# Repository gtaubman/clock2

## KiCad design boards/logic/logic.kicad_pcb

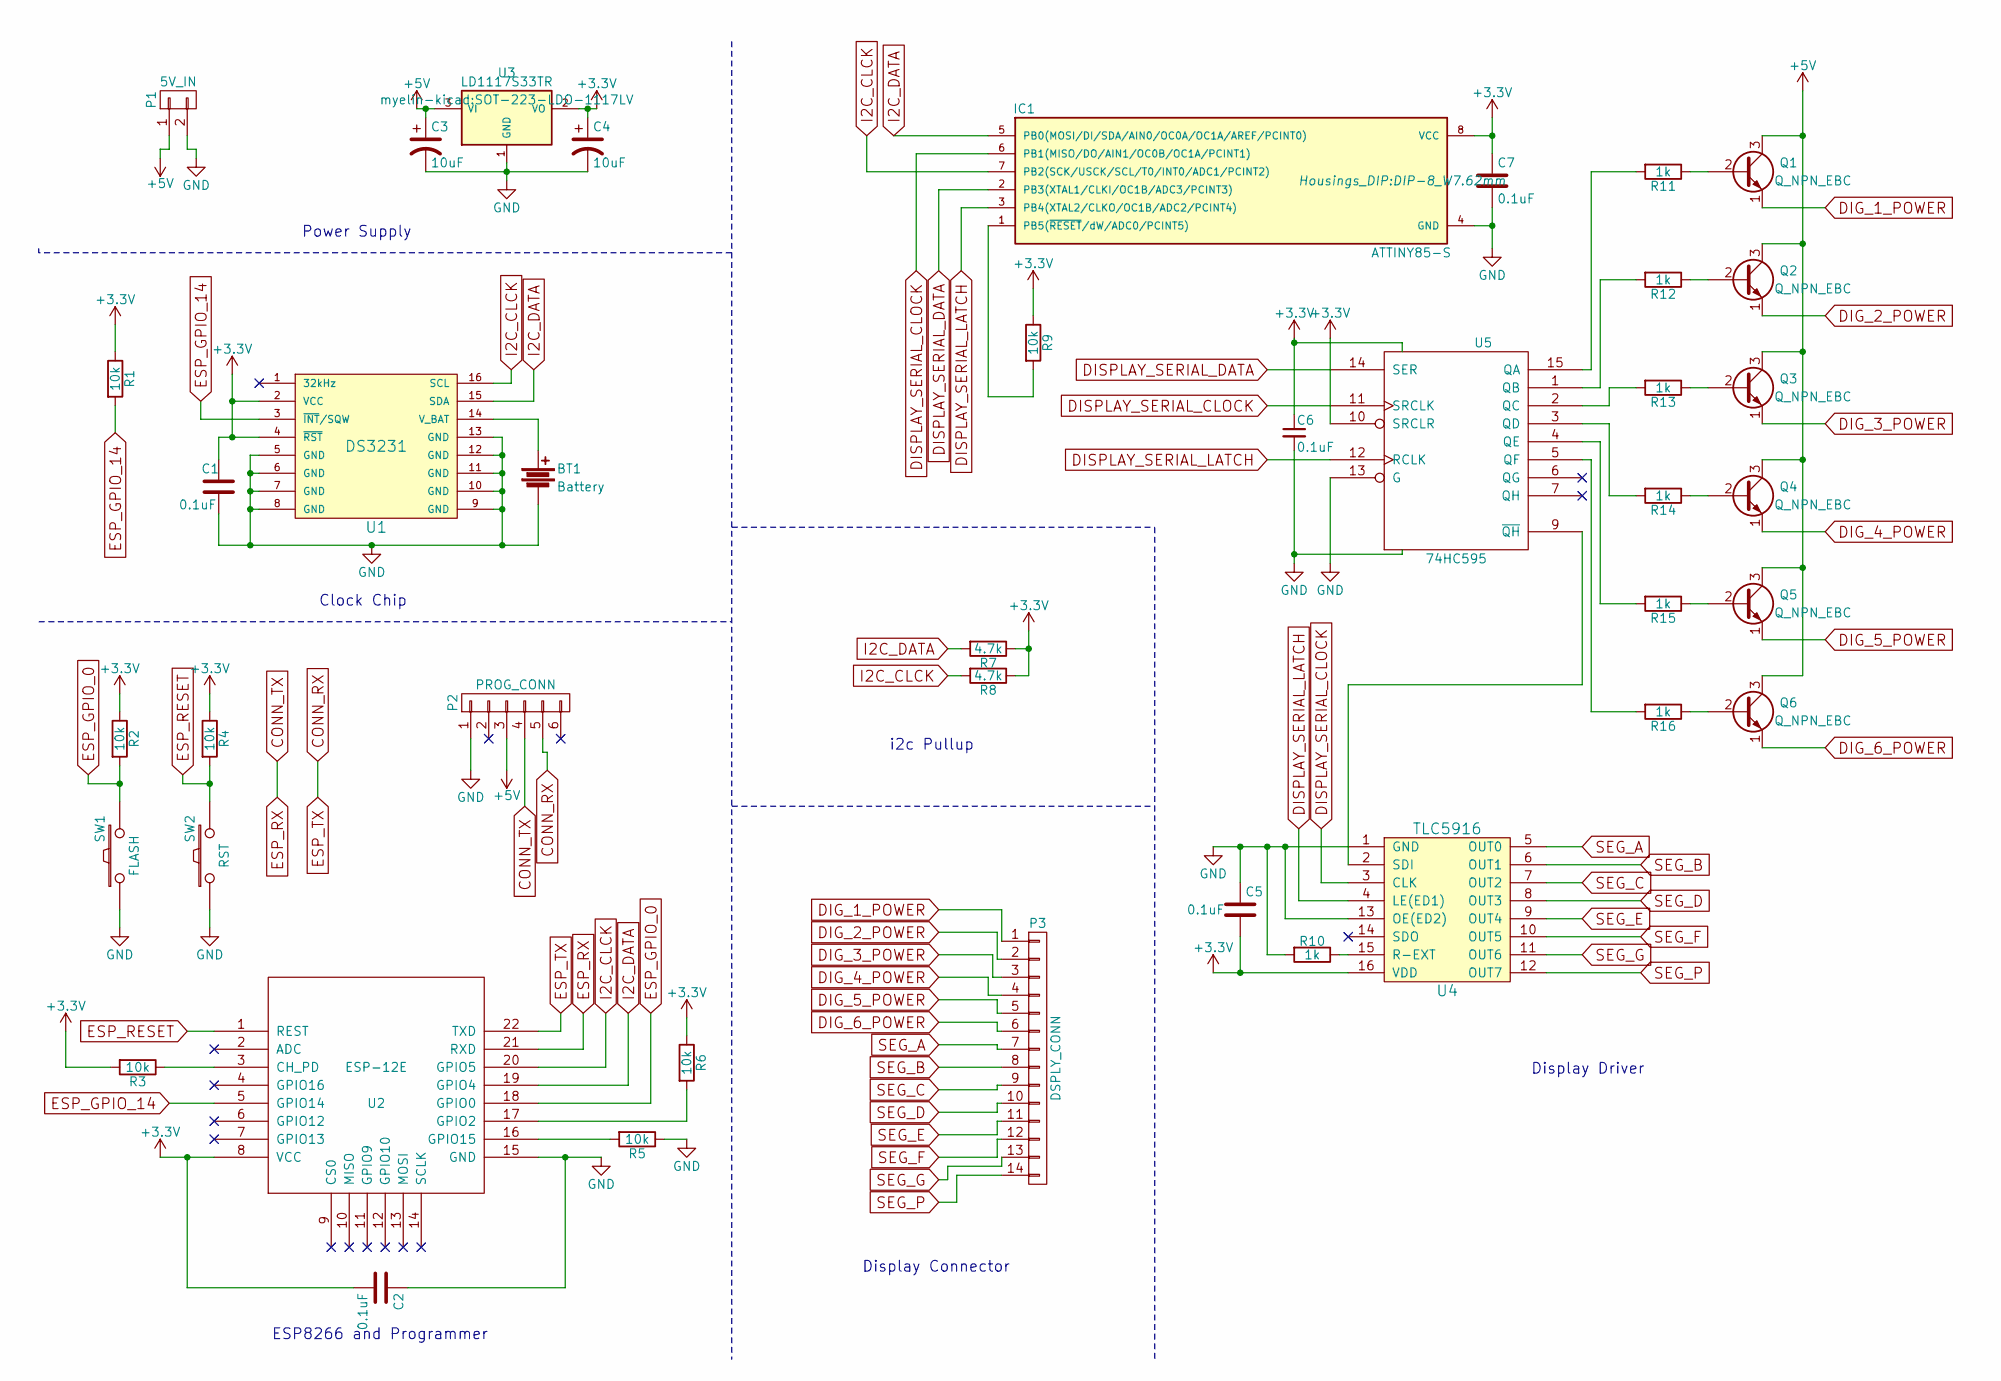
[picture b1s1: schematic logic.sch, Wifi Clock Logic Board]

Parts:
BT1: Battery; BAT_CR1216
C1, C2, C5, C6, C7: 0.1uF; C_Disc_D3_P2.5
C3, C4: 10uF; C_Radial_D5_L6_P2.5
IC1: ATTINY85-S; DIP-8_W7.62mm
P1: 5V_IN; Pin_Header_Straight_1x02
P2: PROG_CONN; Pin_Header_Straight_1x06
P3: DSPLY_CONN; Pin_Header_Straight_1x14
Q1, Q2, Q3, Q4, Q5, Q6: Q_NPN_EBC; TO-92_Inline_Narrow_Oval
R1, R2, R3, R4, R5, R6, R9: 10k; Resistor_Horizontal_RM10mm
R7, R8: 4.7k; Resistor_Horizontal_RM7mm
R10, R11, R12, R13, R14, R15, R16: 1k; Resistor_Horizontal_RM10mm
SW1: FLASH; SW_PUSH_SMALL
SW2: RST; SW_PUSH_SMALL
U1: DS3231; SOIC-16_7.5x10.3mm_Pitch1.27mm
U2: ESP-12E
U3: LD1117S33TR; SOT-223-LDO-1117LV
U4: TLC5916; SOIC-16_3.9x9.9mm_Pitch1.27mm
U5: 74HC595; SOIC-16_3.9x9.9mm_Pitch1.27mm

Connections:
+3V3: C1.1, C2.2, C4.1, C5.2, C6.1, C7.1, IC1.8 (VCC), R1.1, R2.1, R3.2, R4.1, R6.1, R7.1, R8.1, R9.1, U1.2 (VCC), U1.4 (~RST), U2.8 (VCC), U3.2 (VO), U4.16 (VDD), U5.10 (SRCLR), U5.16 (VCC)
+5V: C3.1, P1.1, P2.3, Q1.3 (C), Q2.3 (C), Q3.3 (C), Q4.3 (C), Q5.3 (C), Q6.3 (C), U3.3 (VI)
CONN_RX: P2.5, U2.22 (TXD)
CONN_TX: P2.4, U2.21 (RXD)
DIG_1_POWER: P3.1, Q1.1 (E)
DIG_2_POWER: P3.2, Q2.1 (E)
DIG_3_POWER: P3.3, Q3.1 (E)
DIG_4_POWER: P3.4, Q4.1 (E)
DIG_5_POWER: P3.5, Q5.1 (E)
DIG_6_POWER: P3.6, Q6.1 (E)
DISPLAY_SERIAL_CLOCK: IC1.6 (PB1(MISO/DO/AIN1/OC0B/OC1A/PCINT1)), U4.3 (CLK), U5.11 (SRCLK)
DISPLAY_SERIAL_DATA: IC1.2 (PB3(XTAL1/CLKI/OC1B/ADC3/PCINT3)), U5.14 (SER)
DISPLAY_SERIAL_LATCH: IC1.3 (PB4(XTAL2/CLKO/OC1B/ADC2/PCINT4)), U4.4 (LE(ED1)), U5.12 (RCLK)
ESP_GPIO_0: R2.2, SW1.2, U2.18 (GPIO0)
ESP_GPIO_14: R1.2, U1.3 (~INT~/SQW), U2.5 (GPIO14)
ESP_RESET: R4.2, SW2.2, U2.1 (REST)
GND: BT1.2, C1.2, C2.1, C3.2, C4.2, C5.1, C6.2, C7.2, IC1.4 (GND), P1.2, P2.1, R5.1, R10.2, SW1.1, SW2.1, U1.5 (GND), U1.6 (GND), U1.7 (GND), U1.8 (GND), U1.9 (GND), U1.10 (GND), U1.11 (GND), U1.12 (GND), U1.13 (GND), U2.15 (GND), U3.1 (GND), U4.1 (GND), U4.13 (OE(ED2)), U5.8 (GND), U5.13 (G)
I2C_CLCK: IC1.7 (PB2(SCK/USCK/SCL/T0/INT0/ADC1/PCINT2)), R8.2, U1.16 (SCL), U2.20 (GPIO5)
I2C_DATA: IC1.5 (PB0(MOSI/DI/SDA/AIN0/OC0A/OC1A/AREF/PCI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), R7.2, U1.15 (SDA), U2.19 (GPIO4)
unnamed: BT1.1, U1.14 (V_BAT)
unnamed: IC1.1 (PB5(~RESET~/dW/ADC0/PCINT5)), R9.2
unnamed: Q1.2 (B), R11.1
unnamed: Q2.2 (B), R12.1
unnamed: Q3.2 (B), R13.1
unnamed: Q4.2 (B), R14.1
unnamed: Q5.2 (B), R15.1
unnamed: Q6.2 (B), R16.1
unnamed: R3.1, U2.3 (CH_PD)
unnamed: R5.2, U2.16 (GPIO15)
unnamed: R6.2, U2.17 (GPIO2)
unnamed: R10.1, U4.15 (R-EXT)
unnamed: R11.2, U5.15 (QA)
unnamed: R12.2, U5.1 (QB)
unnamed: R13.2, U5.2 (QC)
unnamed: R14.2, U5.3 (QD)
unnamed: R15.2, U5.4 (QE)
unnamed: R16.2, U5.5 (QF)
unnamed: U4.2 (SDI), U5.9 (~QH)
SEG_A: P3.7, U4.5 (OUT0)
SEG_B: P3.8, U4.6 (OUT1)
SEG_C: P3.9, U4.7 (OUT2)
SEG_D: P3.10, U4.8 (OUT3)
SEG_E: P3.11, U4.9 (OUT4)
SEG_F: P3.12, U4.10 (OUT5)
SEG_G: P3.13, U4.11 (OUT6)
SEG_P: P3.14, U4.12 (OUT7)

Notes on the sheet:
Display Connector
ESP8266 and Programmer
Clock Chip
Power Supply
i2c Pullup
Display Driver

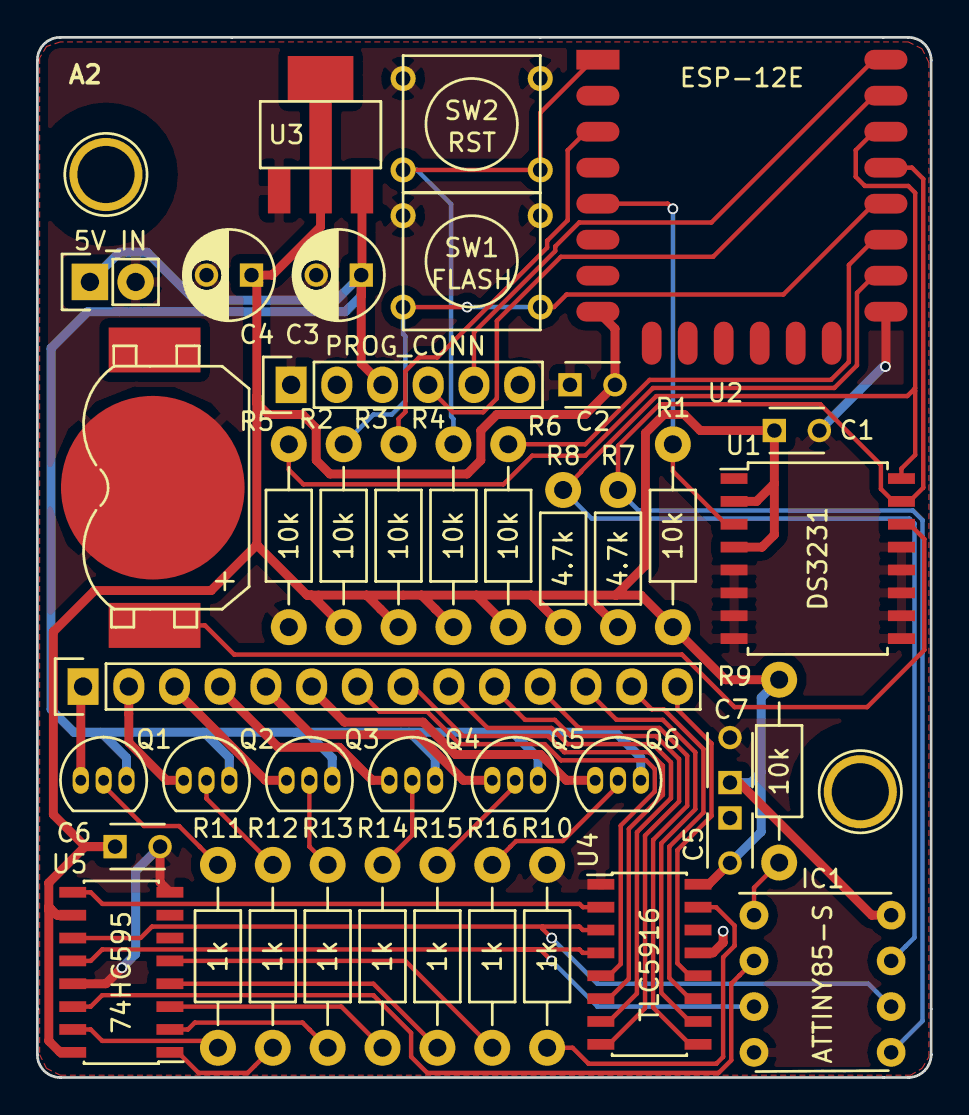
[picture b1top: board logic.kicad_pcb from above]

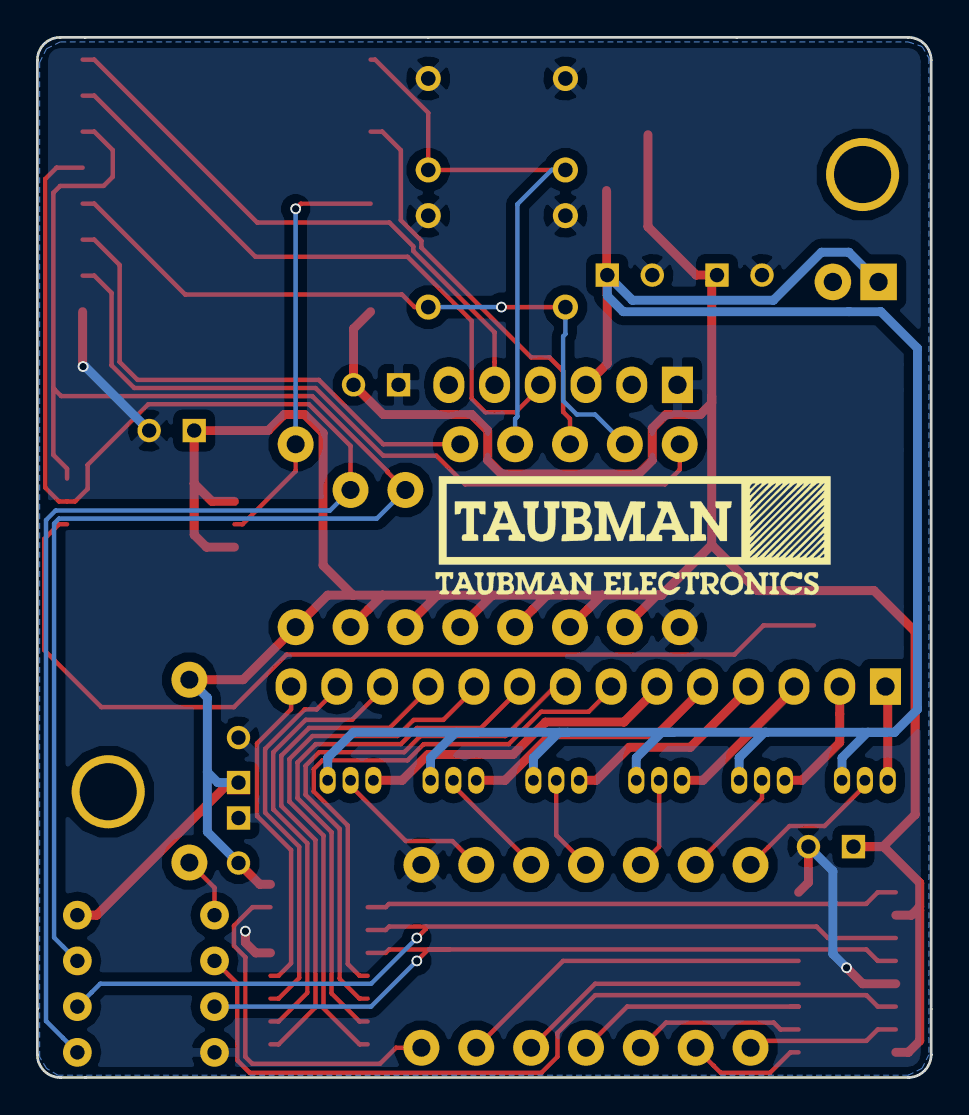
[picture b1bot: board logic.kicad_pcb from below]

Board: 2 copper layers, 49.7 x 57.8 mm, 45 parts (2 on the bottom side), 46 nets.

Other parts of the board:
G1: LOGO; te_22mm_width
G2: LOGO; te_text_22mm_width
REF1, REF2: 1pin

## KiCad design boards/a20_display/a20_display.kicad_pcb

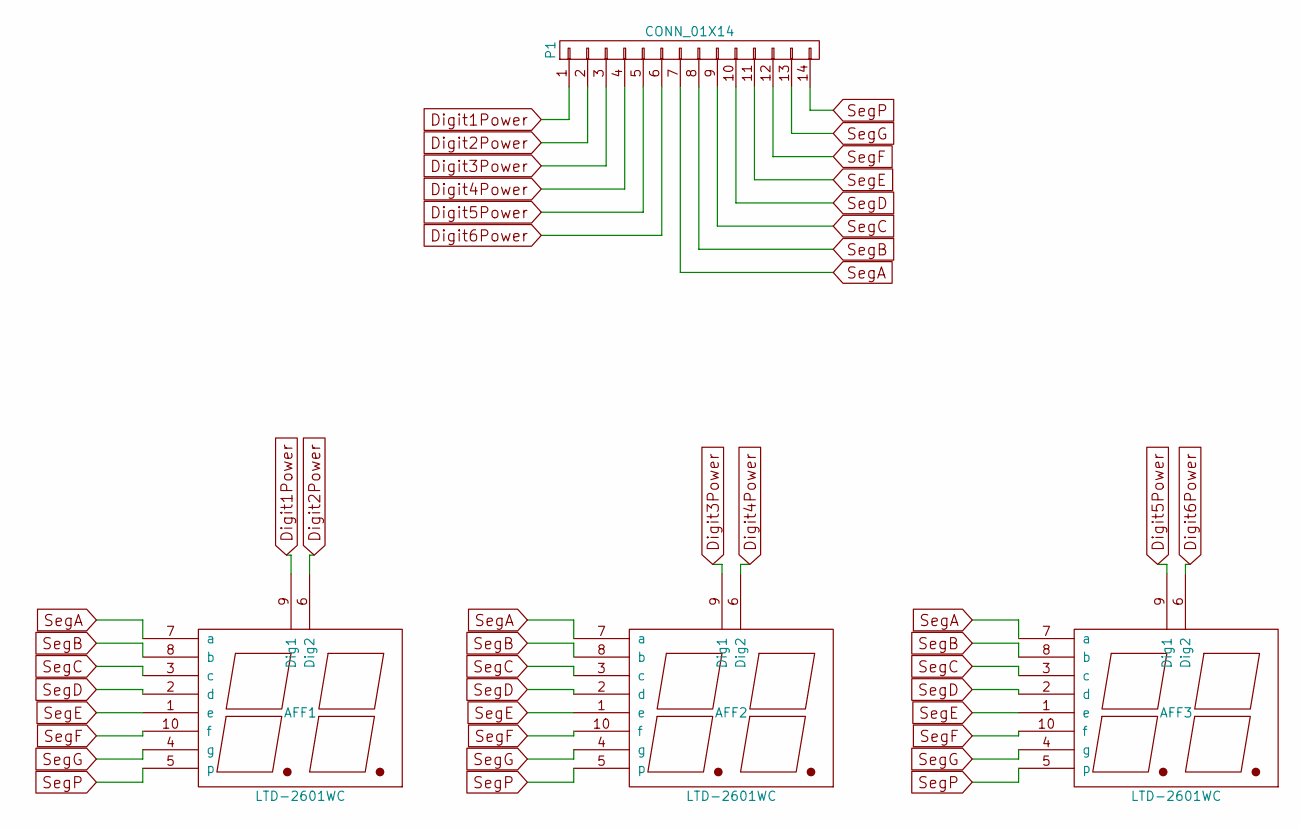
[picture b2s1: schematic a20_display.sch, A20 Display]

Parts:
AFF1, AFF2, AFF3: LTD-2601WC
P1: CONN_01X14; Pin_Header_Straight_1x14

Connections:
Digit1Power: AFF1.9 (Dig1), P1.1
Digit2Power: AFF1.6 (Dig2), P1.2
Digit3Power: AFF2.9 (Dig1), P1.3
Digit4Power: AFF2.6 (Dig2), P1.4
Digit5Power: AFF3.9 (Dig1), P1.5
Digit6Power: AFF3.6 (Dig2), P1.6
SegA: AFF1.7 (a), AFF2.7 (a), AFF3.7 (a), P1.7
SegB: AFF1.8 (b), AFF2.8 (b), AFF3.8 (b), P1.8
SegC: AFF1.3 (c), AFF2.3 (c), AFF3.3 (c), P1.9
SegD: AFF1.2 (d), AFF2.2 (d), AFF3.2 (d), P1.10
SegE: AFF1.1 (e), AFF2.1 (e), AFF3.1 (e), P1.11
SegF: AFF1.10 (f), AFF2.10 (f), AFF3.10 (f), P1.12
SegG: AFF1.4 (g), AFF2.4 (g), AFF3.4 (g), P1.13
SegP: AFF1.5 (p), AFF2.5 (p), AFF3.5 (p), P1.14

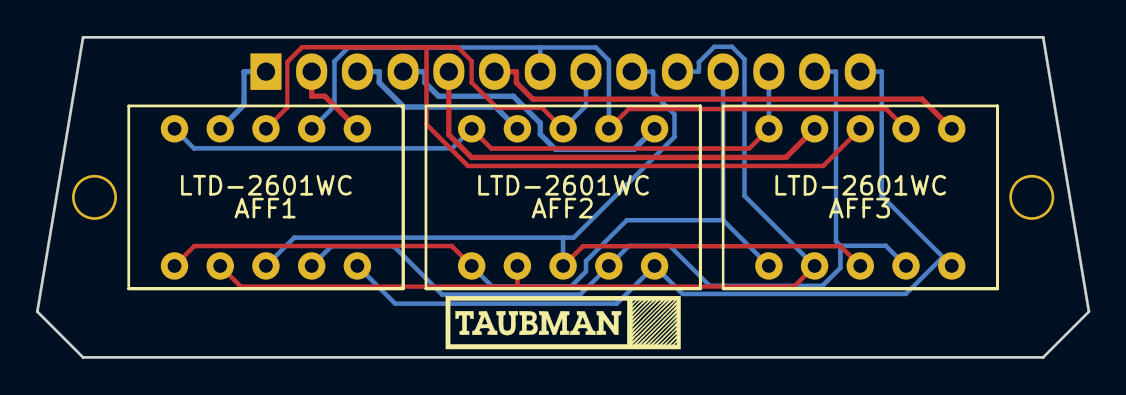
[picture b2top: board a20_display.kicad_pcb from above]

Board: 2 copper layers, 58.4 x 17.8 mm, 4 parts (1 on the bottom side), 14 nets.

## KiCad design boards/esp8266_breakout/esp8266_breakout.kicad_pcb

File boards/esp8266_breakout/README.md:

# ESP8266 ESP 12 Breakout Board

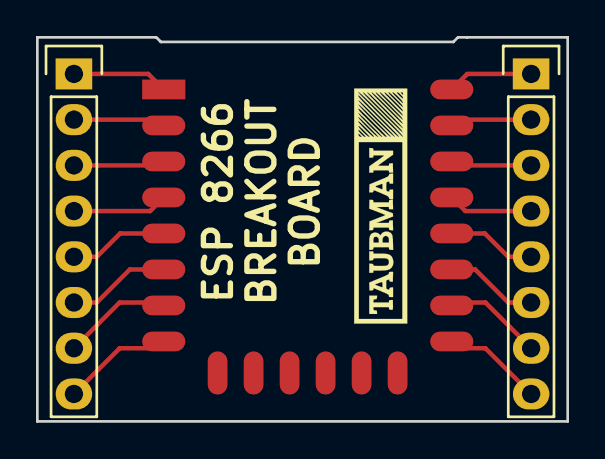
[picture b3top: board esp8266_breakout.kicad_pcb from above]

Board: 2 copper layers, 29.5 x 21.3 mm, 3 parts (0 on the bottom side), 16 nets.

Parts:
P1, P2: CONN_01X08; Pin_Header_Straight_1x08
U1: ESP-12; ESP-12E

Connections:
unnamed: P1.1, U1.1
unnamed: P1.2, U1.2
unnamed: P1.3, U1.3
unnamed: P1.4, U1.4
unnamed: P1.5, U1.5
unnamed: P1.6, U1.6
unnamed: P1.7, U1.7
unnamed: P1.8, U1.8
unnamed: P2.1, U1.22
unnamed: P2.2, U1.21
unnamed: P2.3, U1.20
unnamed: P2.4, U1.19
unnamed: P2.5, U1.18
unnamed: P2.6, U1.17
unnamed: P2.7, U1.16
unnamed: P2.8, U1.15

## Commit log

2016-07-05 Initial commit of in-progress logic board.
2016-07-07 Initial commit of in-progress logic board firmware.
2016-07-07 Remove .DS_Store
2016-07-07 Ignore .DS_Store files.
2016-07-07 Remove another stray DS Store.
2016-07-07 Catch patterns of .DS_Store files.
2016-07-07 Initial commit of Makefile and C file for attiny85 display driver.
2016-07-27 Add an ESP8266 breakout board.
2016-07-27 Add images of the front and back of the ESP8266 breakout.
2016-07-27 Add README for ESP8266 breakout.
2016-07-27 Fix README formatting.
2016-07-31 Update metadata on schematic.
2016-07-31 Schematic image.
2016-07-31 Update ESP8266 README to include schematic.
2016-08-14 Add an A20 display board.
2016-08-15 Fix mounting holes and add back stripes.
2016-08-15 Add a README and front PCB image.
2016-09-07 Add an image of the A20 display schematic.
2016-09-08 Implement digit output and a counter to test the display.
2016-09-10 Implement an i2c receiver portion of the display driver.
2016-09-10 Add SVG images of the display board.
2016-09-11 Add a pullup resistor to CH_PD.
2016-09-11 Remove the level shifter (via zener) from the CONN_TX->ESP_RX connection.
2016-09-11 Wire the 6-bin programming header.
2016-09-11 Use the 8th output of the TLC5916 for the decimal point.
2016-09-11 Add a 5V input to the board, and re-layout the schematic for easier reading.
2016-09-11 Add a missing pullup to the DS3231 interrupt pin, and add some NC symbols.
2016-09-11 Flip the TX/RX on the programming connector.
2016-09-11 Label the connector names.
2016-09-11 Pull up the display driver reset pin to 3.3V.
2016-09-11 Associate footprints with all components.
2016-09-12 Update the footprint for the battery holder and densify the PCB layout.
2016-09-13 Fit all the components into a smaller board footprint.
2016-09-15 Switch the LM1117 footprint to SOT-223.
2016-09-17 Rearrange PCB layout to accomodate mounting screws.
2016-09-17 Add references for the mounting holes to allow spectra output to work.
2016-09-18 Potential final board layout.
2016-09-18 Rearrange silkscreen markers and add TE logo.
2016-09-19 Add GND pours on the front and back copper layers.
2016-09-20 Add final silk screen.
2016-10-26 Commit A1 gerbers for logic board.
2016-10-26 Fix mislabeled 'I2C_DATA' which should have been 'I2C_CLCK'.
2016-10-28 Widened the board a tiny bit, and hand routed the majority of the display system.
2016-10-29 Finished hand routing the board except for ground.
2016-10-29 Small trace adjustments to keep proper spacing.
2016-10-29 Route ESP8266 ground, and add top and bottom ground planes.
2016-10-29 Fix an unconnected ground on the TLC5916 and update the schematic date.
2016-10-29 Add images.
2016-10-29 Move the via for ESP8266 ground to be entirely within the F.Cu fill.
2016-10-29 Add README with images.
2016-10-29 Switch README image URLS to raw image links.
2016-10-29 Change design rules to be within OSHPark tolerances, and update via sizes and locations to be compliant.
2016-10-29 Update front-back-nofill image.
